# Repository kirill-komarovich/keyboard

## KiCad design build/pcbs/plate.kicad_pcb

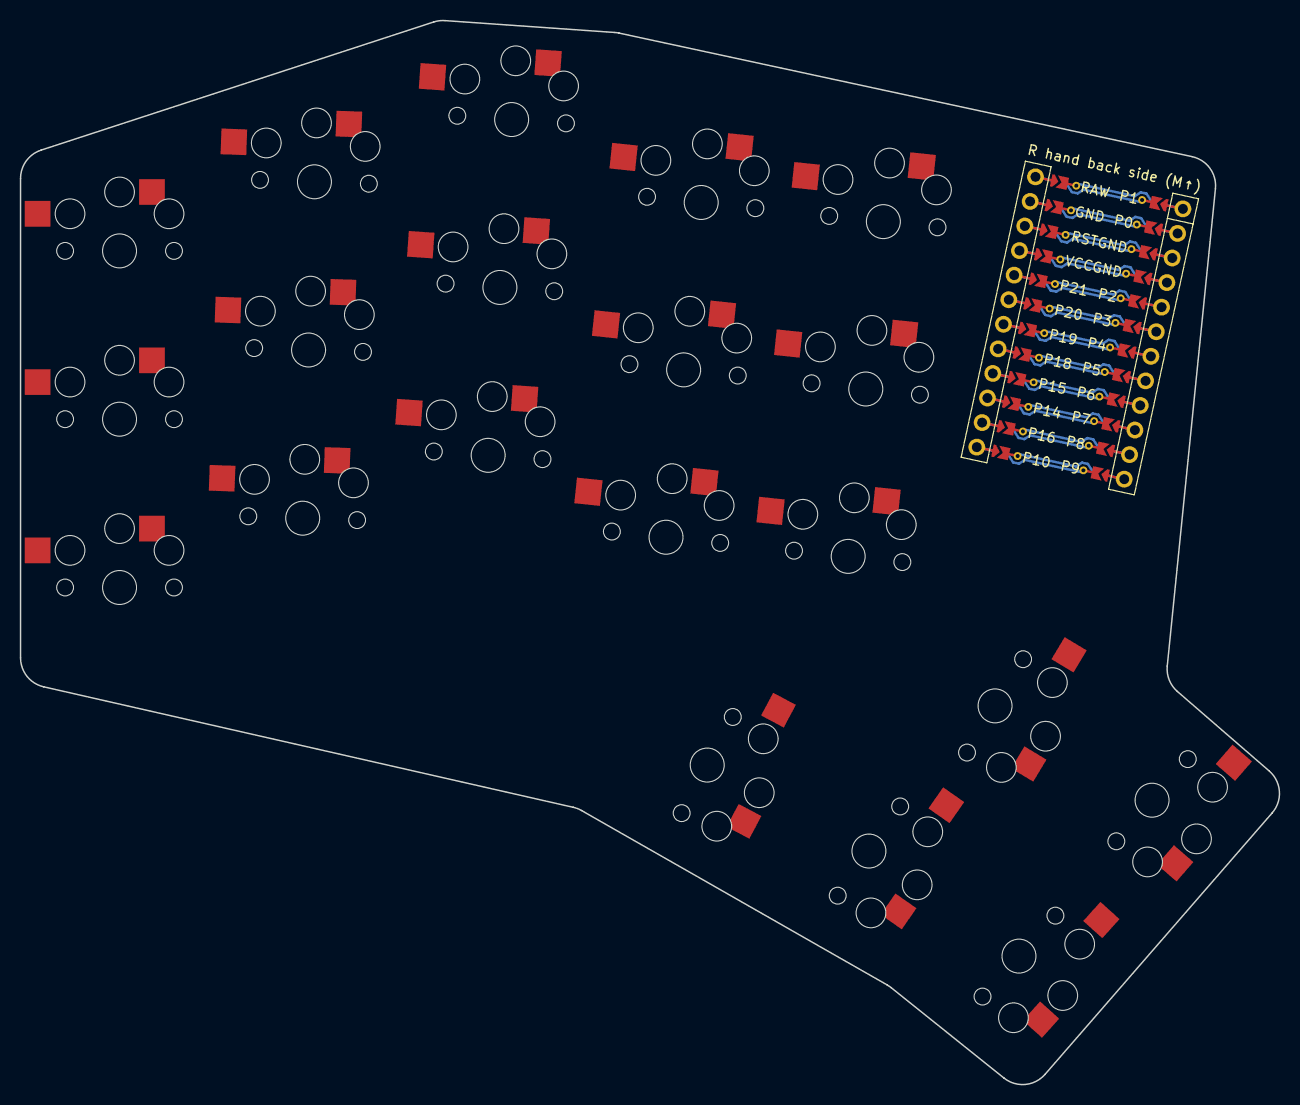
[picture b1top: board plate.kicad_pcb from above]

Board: 2 copper layers, 127.2 x 107.5 mm, 21 parts (0 on the bottom side), 2 nets.

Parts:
MCU1: mcu_nice_nano
S1, S2, S3, S4, S5, S6, S7, S8, S9, S10, S11, S12, S13, S14, S15, S16, S17, S18, S19, S20: PG1350

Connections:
=column_net: S1.1, S2.1, S3.1, S4.1, S5.1, S6.1, S7.1, S8.1, S9.1, S10.1, S11.1, S12.1, S13.1, S14.1, S15.1, S16.1, S17.1, S18.1, S19.1, S20.1
GND: MCU1.103, MCU1.104, MCU1.123, S1.2, S2.2, S3.2, S4.2, S5.2, S6.2, S7.2, S8.2, S9.2, S10.2, S11.2, S12.2, S13.2, S14.2, S15.2, S16.2, S17.2, S18.2, S19.2, S20.2

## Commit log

2023-02-15 Init layout
2023-02-15 Reduce paddings
2023-02-15 Reduce thump paddings
2023-03-26 Add outlines
2023-03-26 Fix build. Add cases
2023-03-26 Fix pcb generation
2023-05-10 Remove one thumb key, update outelines
2023-05-10 Remove wip rgb
2023-05-15 Add EliteC controller
2025-07-01 Update ergogen
2025-07-01 Add nicenano controller
2025-07-01 Remove elite c footprint
2025-07-01 Bump @babel/runtime from 7.21.0 to 7.27.6
    Bumps [@babel/runtime](https://github.com/babel/babel/tree/HEAD/packages/babel-runtime) from 7.21.0 to 7.27.6.
    - [Release notes](https://github.com/babel/babel/releases)
    - [Changelog](https://github.com/babel/babel/blob/main/CHANGELOG.md)
    - [Commits](https://github.com/babel/babel/commits/v7.27.6/packages/babel-runtime)
    ---
    updated-dependencies:
